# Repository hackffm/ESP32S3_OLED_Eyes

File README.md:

# ESP32S3_OLED_Eyes
Touch-sensitive OLED Eyes for ESP32-S3 modules based on playfultechnology / esp32-eyes. A badge from Hackerspace-FFM.de that shows eye animation and name on the OLED display.

This is a picture of the badge: 

More info in [Hackerspace-FFM Wiki](https://www.hackerspace-ffm.de/wiki/index.php?title=Hackerspace-FFM_Badge)

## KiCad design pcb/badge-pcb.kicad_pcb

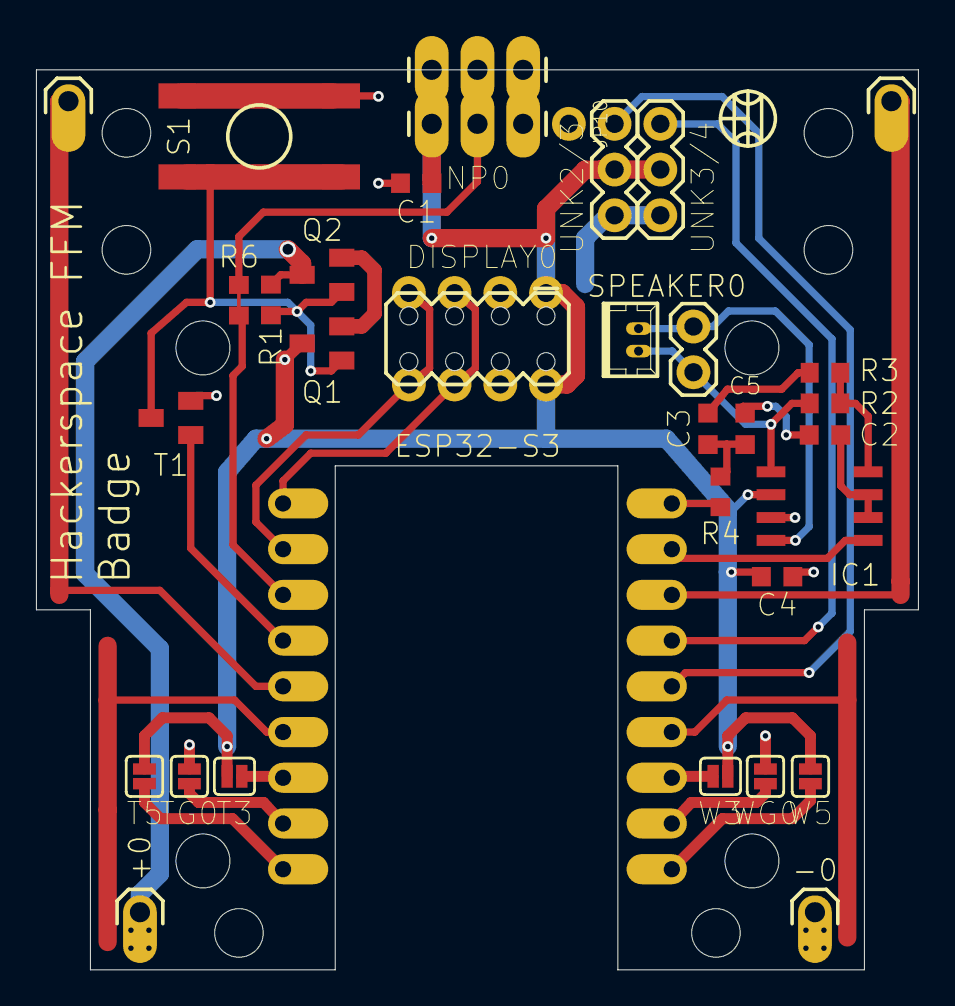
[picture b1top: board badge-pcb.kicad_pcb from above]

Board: 2 copper layers, 49.0 x 50.0 mm, 44 parts (0 on the bottom side), 28 nets.

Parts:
+0: M01OFFSET; 1X01_OFFSET
-0: M01OFFSET; 1X01_OFFSET
C1, C2, C3, C4: 1µF; C0603K
C5: 1nF; C0603K
DISPLAY0: 2X04DRILL; 2X4-DRILL
ESP32-S3: ESP32-S3-MINI
IC1: LM4861M; SOIC8
J1: 1X02
J3: 455-1750-1-ND; 1X03_LONGPADS
JP9, JP11: M01OFFSET; 1X01_OFFSET
JP10: M01PTH; M01_1X01
NP0: 455-1750-1-ND; 1X03_LONGPADS
Q1, Q2: AO3415A; SOT23-3PIN
R1, R2, R3: 22K; R0603
R4: 4K7; R0603
R6: 470R; R0603
S1: JTP-1138EM
SPEAKER0: 53047-02
T1: MMUN2213LT1G; SOT23
T3, T5: JUMPER-SMT_2_NO_SILK; SMT-JUMPER_2_NO_SILK
TG0: JUMPER-SMT_2_NO_SILK; SMT-JUMPER_2_NO_SILK
UNK2/3, UNK3/4: 455-1750-1-ND; 1X03
UNK_HOLE_0: dummyfp0
UNK_HOLE_1: dummyfp1
UNK_HOLE_2: dummyfp2
UNK_HOLE_3: dummyfp3
UNK_HOLE_4: dummyfp4
UNK_HOLE_5: dummyfp5
UNK_HOLE_6: dummyfp6
UNK_HOLE_7: dummyfp7
UNK_HOLE_8: dummyfp8
UNK_HOLE_9: dummyfp9
W3, W5: JUMPER-SMT_2_NO_SILK; SMT-JUMPER_2_NO_SILK
WG0: JUMPER-SMT_2_NO_SILK; SMT-JUMPER_2_NO_SILK

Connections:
2/3: ESP32-S3.2, UNK2/3.3
3/4: ESP32-S3.3, UNK3/4.3
AUDIO: ESP32-S3.6, R4.2
B: ESP32-S3.4, JP9.1
D: ESP32-S3.11, JP11.1
GND: -0.1, C1.2, C2.2, C4.2, C5.2, DISPLAY0.3A, DISPLAY0.4A, IC1.7, J3.1, JP10.1, NP0.1, S1.3, S1.4, T1.2, TG0.1, UNK2/3.1, UNK3/4.1, WG0.1
unnamed: ESP32-S3.3V3, W3.2
unnamed: ESP32-S3.13, T3.2
unnamed: ESP32-S3.RX, TG0.2
unnamed: ESP32-S3.GND, WG0.2
unnamed: Q1.2, Q2.2
unnamed: ESP32-S3.5V, W5.2
unnamed: +0.1, Q2.3, R1.2
unnamed: Q1.1, Q2.1, R1.1, S1.1, S1.2, T1.3
unnamed: IC1.8, J1.2, SPEAKER0.2
unnamed: ESP32-S3.TX, T5.1
unnamed: IC1.5, J1.1, R2.2, SPEAKER0.1
unnamed: IC1.4, R2.1, R3.2
unnamed: C2.1, IC1.2, IC1.3
unnamed: C3.2, R3.1
unnamed: C3.1, C5.1, R4.1
unnamed: J3.2, NP0.2, R6.2
NP: ESP32-S3.9, R6.1
PWR: ESP32-S3.10, T1.1
SCK: DISPLAY0.5A, DISPLAY0.6A, ESP32-S3.7
SDA: DISPLAY0.7A, DISPLAY0.8A, ESP32-S3.8
SHUTDOWN: ESP32-S3.5, IC1.1
VCC: C1.1, C4.1, DISPLAY0.1A, DISPLAY0.2A, IC1.6, J3.3, NP0.3, Q1.3, T3.1, T5.2, UNK2/3.2, UNK3/4.2, W3.1, W5.1

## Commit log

2025-02-24 Add touch control
2025-02-24 Boot toggles emos
2025-03-09 Audiotests
2025-03-24 Big cleanup #1
2025-03-26 cleanup2
2025-03-26 Clean 3
2025-03-27 Ani-Cycle
2025-03-28 Add customizable Badge name
2025-03-28 Web OTA
2025-03-28 start sound changed
2025-03-28 some face
2025-03-28 in terminal naming mode switch to screen mode name
2025-03-30 minor stuff
2025-04-04 Touch to lib
2025-04-09 Post build creates pull-FW
2025-04-20 More clean-up, Badge should be able to open/close doors in Hackerspace via EspNow.
2025-05-05 Changed to pioarduino
2025-05-09 Updates for door access
2025-06-20 Big cleanup
2025-06-24 Add: comments in README.md
2025-10-05 drawCenteredUTF8Text added, formats Badge Name nicely big fully automatic.
2025-10-06 FW Update possible by holding button when no display and blinking red/blue.
2025-10-08 Radar started, badges now Tx its name.
2025-10-09 A little docu.
